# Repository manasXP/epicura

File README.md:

# Epicura

An autonomous countertop kitchen robot that cooks one-pot meals using AI vision, robotic stirring, and precise induction heat control. Designed for compact Indian kitchens, under 2kW power draw.

```
┌─────────────────────────────────────────────────────────────────────┐
│                    Epicura System Overview                          │
│                                                                     │
│  ┌──────────────────────┐        ┌──────────────────────┐           │
│  │  Raspberry Pi CM5    │        │  STM32 MCU           │           │
│  │  (Yocto Linux)       │◄──────►│  (FreeRTOS)          │           │
│  │  - Recipe Engine     │  UART  │  - PID Control       │           │
│  │  - CV Pipeline       │  /SPI  │  - Servo Driver      │           │
│  │  - Kivy UI           │        │  - Sensor Polling    │           │
│  │  - Cloud Sync        │        │  - Safety Watchdog   │           │
│  └──────────┬───────────┘        └──────────┬───────────┘           │
│             │                               │                       │
│  ┌──────────▼───────────┐        ┌──────────▼───────────┐           │
│  │  10" Touchscreen     │        │  Induction Heater    │           │
│  │  HD Camera           │        │  Servo Arm           │           │
│  │  WiFi/BT             │        │  Load Cells          │           │
│  │                      │        │  NTC + IR Sensors    │           │
│  └──────────────────────┘        └──────────────────────┘           │
└─────────────────────────────────────────────────────────────────────┘
```

## Key Features

- **Autonomous Cooking** — Hands-off operation after ingredient loading with state machine recipe execution
- **AI Vision** — Overhead camera with TFLite MobileNetV2 for food color/texture analysis and cooking stage detection
- **Induction PID Control** — 1,800W microwave induction surface (CAN bus) with closed-loop PID, ±5°C accuracy
- **Robotic Stirring Arm** — Single-axis servo arm with multiple stir patterns and auto-scraping
- **Three-Subsystem Dispensing** — Seasonings (servo-gated hoppers), coarse ingredients (linear actuator trays), liquids (peristaltic pumps)
- **Touchscreen + Mobile Apps** — 10" Kivy touchscreen UI, native iOS (Swift) and Android (Kotlin) companion apps
- **100+ Indian Recipes** — Curries, dal, rice, biryani with regional variations and dietary customization
- **Cloud + Offline** — Cloud-updatable recipe library with full local fallback

## Hardware Architecture

| Component | Part | Purpose |
|-----------|------|---------|
| Compute (AI) | Raspberry Pi CM5 (4GB, 64GB eMMC) | Vision, recipe engine, UI, cloud sync |
| Compute (Control) | STM32G474 (Cortex-M4F, 170 MHz) | PID, servo driver, sensor polling, safety |
| Carrier Board | CM5IO (official RPi IO board) | CM5 carrier with all breakouts |
| Camera | IMX219 (8MP) | Food stage detection via CV |
| IR Thermometer | MLX90614 | Non-contact food surface temp |
| Load Cells | 4× strain gauge + HX711 | Weight-based dispensing verification |
| Induction Surface | 1,800W commercial module | CAN bus controlled cooking heat |
| Servo Arm | 24V BLDC motor (integrated ESC) | Stirring and scraping |
| Display | 10" 1280×800 capacitive | Kivy touchscreen UI |

## Software Stack

### CM5 (Yocto Linux + Docker Compose)

- **Database**: PostgreSQL 16 — same schema as cloud
- **MQTT**: Mosquitto broker with cloud bridge
- **Backend API**: Fastify (Node.js/TypeScript) — same codebase as cloud (minus admin module)
- **Recipe Engine**: Python — YAML parsing, state machine
- **CV Pipeline**: OpenCV + TFLite MobileNetV2 INT8
- **UI**: Kivy — touchscreen interface
- **OTA Updates**: swupdate with A/B partitions

### STM32 (FreeRTOS)

- 4 tasks: PID (100 Hz), servo (50 Hz), sensor (10 Hz), comms (20 Hz)
- C (MISRA subset for safety-critical paths)
- Hardware watchdog, thermal cutoffs, e-stop relay

## Project Status

**Phase:** Design & Documentation

Comprehensive documentation exists across 30+ documents covering hardware, software, subsystems, compliance, PCB design, backend, APIs, mobile apps, and project management.

See [`docs/README.md`](__Workspaces/Epicura/docs/README.md) for the full documentation index.

## Repositories

| Repository                                                          | Stack                          | Purpose                                                               |
| ------------------------------------------------------------------- | ------------------------------ | --------------------------------------------------------------------- |
| **[epicura](https://github.com/manasXP/epicura)**                   | Markdown + KiCAD 9             | Documentation, specifications, PCB design (this repo)                 |
| **[epicura-firmware](https://github.com/manasXP/epicura-firmware)** | C (FreeRTOS, STM32 HAL)        | STM32G474RE real-time control — PID, servo, sensors, CAN, safety      |
| **[epicura-cm5](https://github.com/manasXP/epicura-cm5)**           | Python (Docker Compose)        | CM5 services — recipe engine, CV pipeline, Kivy UI, bridge, Yocto BSP |
| **[epicura-api](https://github.com/manasXP/epicura-api)**           | TypeScript (Fastify + Next.js) | Cloud API server and admin portal monorepo                            |
| **[epicura-ios](https://github.com/manasXP/epicura-ios)**           | Swift (SwiftUI)                | iOS companion app — BLE pairing, recipes, live cooking                |
| **[epicura-android](https://github.com/manasXP/epicura-android)**   | Kotlin (Jetpack Compose)       | Android companion app                                                 |

See [Repository Plan](02-Repository-Plan.md) for directory structures, CI/CD, and cross-repo dependencies.

## Estimated BOM

~$614 for prototype. See [Total Component Cost](__Workspaces/Epicura/docs/08-Components/04-Total-Component-Cost.md) for breakdown.

## Development Roadmap

| Phase | Duration | Deliverables |
|-------|----------|--------------|
| Prototype | 3–6 months | Hardware prototype, basic recipe execution, vision PoC |
| Alpha | 3–6 months | Core features, 20+ recipes, app integration, safety testing |
| Beta | 3–6 months | 100+ recipes, field testing, regulatory pre-compliance |
| Production | 3–6 months | Manufacturing, certifications, market launch |

## License

[Apache License 2.0](LICENSE)

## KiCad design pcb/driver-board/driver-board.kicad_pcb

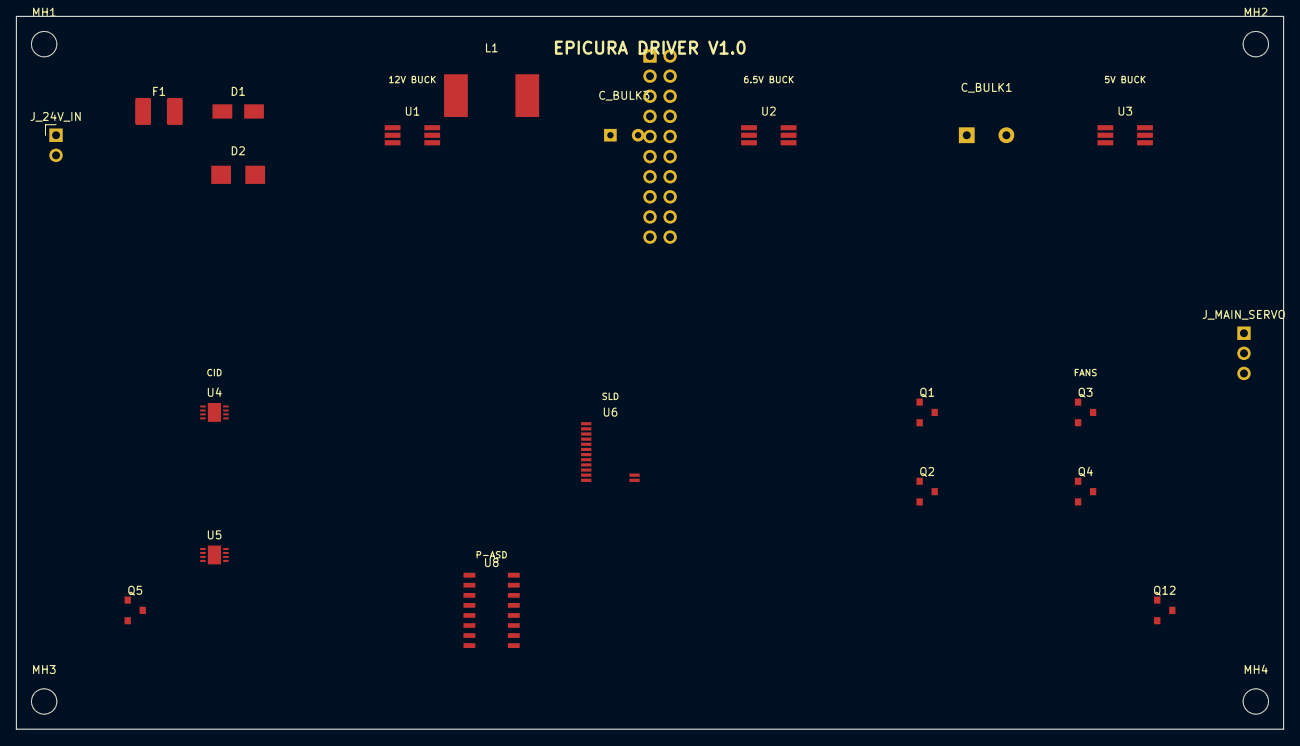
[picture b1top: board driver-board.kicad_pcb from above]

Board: 4 copper layers, 160.0 x 90.0 mm, 26 parts (1 on the bottom side), 23 nets, no tracks yet.

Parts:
C_BULK1: 470uF; CP_Radial_D10.0mm_P5.00mm
C_BULK3: 100uF; CP_Radial_D8.0mm_P3.50mm
D1: SS54; D_SMA
D2: SMBJ24A; D_SMB
F1: 5A; Fuse_1812_4532Metric
J_24V_IN: XT30; PinHeader_1x02_P2.54mm_Vertical
J_MAIN_SERVO: DS3225; PinHeader_1x03_P2.54mm_Vertical
J_STACK: Stacking_Connector; PinHeader_2x20_P2.54mm_Vertical
L1: 33uH; L_Sumida_CDRH104R
MH1, MH2, MH3, MH4: MountingHole_3.2mm_M3
Q1, Q2, Q3, Q4, Q5: IRLML6344; SOT-23
Q12: 2N7002; SOT-23
U1, U2, U3: MP1584EN; SOT-23-8_Handsoldering
U4, U5: DRV8876; DFN-8-1EP_3x3mm_P0.5mm_EP1.66x2.38mm
U6: TB6612FNG; SSOP-24_5.3x8.2mm_P0.65mm
U8: PCF8574; SOIC-16_3.9x9.9mm_P1.27mm

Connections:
24V_INT: D1.2 (A), D2.2 (A), F1.2, L1.1, U1.1 (IN), U1.6 (SW), U2.1 (IN), U2.6 (SW), U3.1 (IN), U3.6 (SW)
+3V3: J_STACK.2 (3V3), U4.7 (VCC), U5.7 (VCC), U6.8 (VCC), U8.16 (VDD)
+6V5: C_BULK1.1, J_MAIN_SERVO.2 (VCC), U2.5 (OUT)
+12V: C_BULK3.1, L1.2, U1.5 (OUT), U4.1 (VM), U5.1 (VM), U6.7 (VM)
+24V: F1.1, J_24V_IN.1
BUZZER_PWM: J_STACK.18 (BUZZER_PWM), Q12.3 (D)
CID_LACT1_EN: J_STACK.5 (CID_LACT1_EN), U4.6 (EN)
CID_LACT1_PH: J_STACK.6 (CID_LACT1_PH), U4.5 (PH)
CID_LACT2_EN: J_STACK.7 (CID_LACT2_EN), U5.6 (EN)
CID_LACT2_PH: J_STACK.8 (CID_LACT2_PH), U5.5 (PH)
FAN1_PWM: J_STACK.15 (FAN1_PWM), Q3.3 (D)
FAN2_PWM: J_STACK.16 (FAN2_PWM), Q4.3 (D)
GND: C_BULK1.2, C_BULK3.2, D1.1 (K), D2.1 (K), J_24V_IN.2, J_MAIN_SERVO.1 (GND), J_STACK.1 (GND), J_STACK.20 (GND), Q1.2 (S), Q2.2 (S), Q3.2 (S), Q4.2 (S), Q5.2 (S), Q12.2 (S), U1.2 (GND), U1.4 (EN), U2.2 (GND), U2.4 (EN), U3.2 (GND), U3.4 (EN), U4.4 (GND), U4.8 (nSLEEP), U4.9 (EP), U5.4 (GND), U5.8 (nSLEEP), U5.9 (EP), U6.5 (AI2), U6.6 (GND), U6.9 (STBY), U6.10 (BI2), U8.1 (A0), U8.2 (A1), U8.3 (A2), U8.8 (GND), U8.11 (P6), U8.12 (P7), U8.13 (INT)
I2C_SCL: J_STACK.3 (SCL), U8.14 (SCL)
I2C_SDA: J_STACK.4 (SDA), U8.15 (SDA)
MAIN_SERVO_PWM: J_MAIN_SERVO.3 (PWM), J_STACK.17 (MAIN_SERVO_PWM)
PASD_PUMP_PWM: J_STACK.19 (PASD_PUMP_PWM), Q5.3 (D)
SLD_PUMP1_DIR: J_STACK.10 (SLD_PUMP1_DIR), U6.4 (AI1)
SLD_PUMP1_PWM: J_STACK.9 (SLD_PUMP1_PWM), U6.3 (PWMA)
SLD_PUMP2_DIR: J_STACK.12 (SLD_PUMP2_DIR), U6.11 (BI1)
SLD_PUMP2_PWM: J_STACK.11 (SLD_PUMP2_PWM), U6.12 (PWMB)
SLD_SOL1_EN: J_STACK.13 (SLD_SOL1_EN), Q1.3 (D)
SLD_SOL2_EN: J_STACK.14 (SLD_SOL2_EN), Q2.3 (D)

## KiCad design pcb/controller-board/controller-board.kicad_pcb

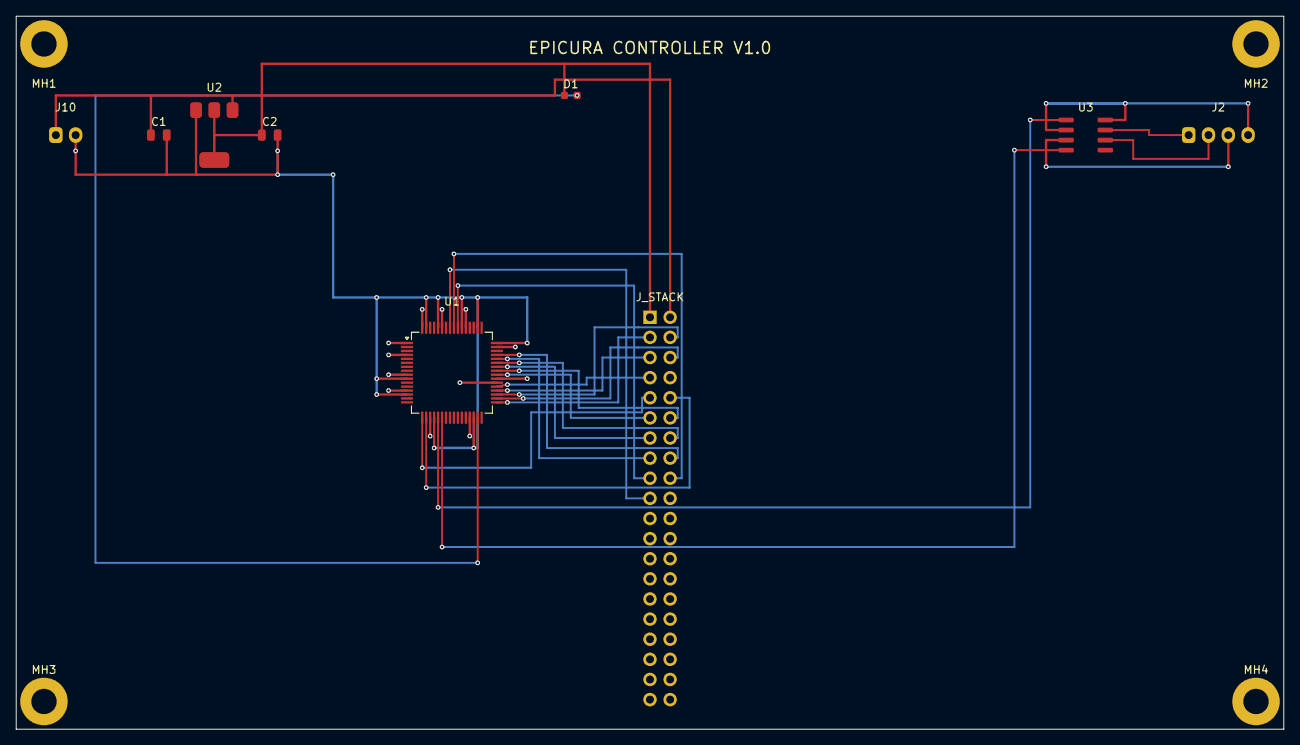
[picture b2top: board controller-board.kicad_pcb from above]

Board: 4 copper layers, 160.0 x 90.0 mm, 13 parts (0 on the bottom side), 24 nets.

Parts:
C1, C2: 10uF; C_0805_2012Metric
D1: LED; LED_0603_1608Metric
J2: CAN; JST_XH_B4B-XH-A_1x04_P2.50mm_Vertical
J10: Power; JST_XH_B2B-XH-A_1x02_P2.50mm_Vertical
J_STACK: Stacking; PinHeader_2x20_P2.54mm_Vertical
MH1, MH2, MH3, MH4: MountingHole_3.2mm_M3; MountingHole_3.2mm_M3_Pad_Via
U1: STM32G474RET6; LQFP-64_10x10mm_P0.5mm
U2: AMS1117-3.3; SOT-223-3_TabPin2
U3: SN65HVD230; SOIC-8_3.9x4.9mm_P1.27mm

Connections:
+3V3: C2.1, D1.1, J2.3, J_STACK.1, U1.1, U1.4, U1.9, U1.13, U1.19, U1.29, U1.38, U1.47, U1.53, U1.59, U1.64, U2.2, U3.3
+5V: C1.1, J10.1, J_STACK.2, U2.3
CAN_H: J2.1, U3.7
CAN_L: J2.2, U3.6
CAN_RX: U1.22, U3.4
CAN_TX: U1.21, U3.1
ESTOP: J_STACK.19, U1.57
GND: C1.2, C2.2, J2.4, J10.2, J_STACK.8, J_STACK.20, J_STACK.39, J_STACK.40, MH1.1, MH2.1, MH3.1, MH4.1, U1.10, U1.14, U1.20, U1.30, U1.39, U1.48, U1.50, U1.54, U1.60, U1.63, U2.1, U3.2, U3.8
HX711_DOUT: J_STACK.16, U1.45
HX711_SCK: J_STACK.15, U1.44
I2C_SCL: J_STACK.9, U1.17
I2C_SDA: J_STACK.10, U1.18
NTC_AMB: J_STACK.14, U1.43
NTC_COIL: J_STACK.13, U1.42
POT_DET: J_STACK.18, U1.56
PUMP_PWM: J_STACK.12, U1.41
RELAY_DRV: J_STACK.17, U1.55
SERVO_PWM: J_STACK.11, U1.40
SPI_IRQ: J_STACK.7, U1.37
SPI_MISO: J_STACK.4, U1.35
SPI_MOSI: J_STACK.5, U1.36
SPI_NSS: J_STACK.3, U1.33
SPI_SCK: J_STACK.6, U1.34
STATUS_LED: D1.2, U1.31

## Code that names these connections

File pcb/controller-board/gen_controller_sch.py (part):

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x, y = u3_abs(10.16, 2.54)
wx = x + 10.16
add_wire(x, y, wx, y)
add_label("CAN_L", wx, y, 0)

# U3 pin 7 (CANH) - to R_TERM and J2
x, y = u3_abs(10.16, 7.62)
wx = x + 10.16
add_wire(x, y, wx, y)
add_label("CAN_H", wx, y, 0)

# R_TERM (120Ω) - connects between CAN_H and CAN_L
# Moved to (243.84, 31.75) to avoid wire overlap with U3 pin wires
# R pin 1 at (0, 3.81, 270) → abs (243.84, 31.75-3.81) = (243.84, 27.94)
# R pin 2 at (0, -3.81, 90) → abs (243.84, 31.75+3.81) = (243.84, 35.56)
add_label("CAN_H", 243.84, 27.94, 0)
add_label("CAN_L", 243.84, 35.56, 0)

# J2 CAN (Conn_01x04) at (240.03, 35.56)
# Pin 1 at (-5.08, 2.54) → abs (234.95, 33.02) → CAN_H
# Pin 2 at (-5.08, 0) → abs (234.95, 35.56) → CAN_L
# Pin 3 at (-5.08, -2.54) → abs (234.95, 38.1) → GND
# Pin 4 at (-5.08, -5.08) → abs (234.95, 40.64) → +5V (optional)
j2_abs = lambda p: (240.03 - 5.08, 35.56 - (2.54 * (2 - (p-1))))  # simplified
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# Pin 1: at (-5.08, 2.54, 0), Pin 2: at (-5.08, 0, 0), Pin 3: at (-5.08, -2.54, 0), Pin 4: at (-5.08, -5.08, 0)
x1, y1 = 240.03 - 5.08, 35.56 - 2.54  # Pin 1
add_wire(x1, y1, x1 - 10.16, y1)
add_label("CAN_H", x1 - 10.16, y1, 0)

x2, y2 = 240.03 - 5.08, 35.56  # Pin 2
add_wire(x2, y2, x2 - 10.16, y2)
add_label("CAN_L", x2 - 10.16, y2, 0)

x3, y3 = 240.03 - 5.08, 35.56 + 2.54  # Pin 3
add_power("GND", x3, y3)
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sym_instances.append(f'    (path "/{uid()}" (reference "R5") (unit 1) (value "10k") (footprint "Resistor_SMD:R_0402_1005Metric"))')

# R6 LED resistor (330Ω) + D1 LED
# STATUS_LED label connects from MCU PC13 to R6 pin 1, R6 pin 2 to D1 anode, D1 cathode to GND
rx, ry = snap(88), 50.8
rp1 = (rx, ry - 3.81)
rp2 = (rx, ry + 3.81)
add_label("STATUS_LED", rp1[0], rp1[1], 0)
# Connect R6 pin 2 to LED_ANODE
add_label("LED_ANODE", rp2[0], rp2[1], 0)

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
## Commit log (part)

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2026-02-15 Add Apache 2.0 license
2026-02-15 Add README with project overview, architecture, and roadmap
2026-02-21 Add files via upload
    Add controller + driver schematics, BOM
2026-02-21 Add files via upload
    Finalize schematics: 0 ERC errors, subsystem boxes added
2026-02-22 Add files via upload
    All #146 items resolved. ERC: 0 errors.
    Critical fixes:
    - D3 + D4 (PRTR5V0U2X) — ESD protection added on SPI and safety lines
    - SJ1 solder jumper — PB3 IRQ/SWO select added
    - RELAY_COIL+ — connected to +5V rail
    Minor fixes:
2026-02-22 Add files via upload
    fix. sorry for the bugs
2026-03-02 Fixed all containers in CM5
